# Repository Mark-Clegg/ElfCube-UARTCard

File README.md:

# Elf-Cube - UART Card
Simple retro computer based on the 1802 series of processors.

Provides serial I/O to the ElfCube using either the onboard DB-9 connector, or via the USB connector on the Backplane.

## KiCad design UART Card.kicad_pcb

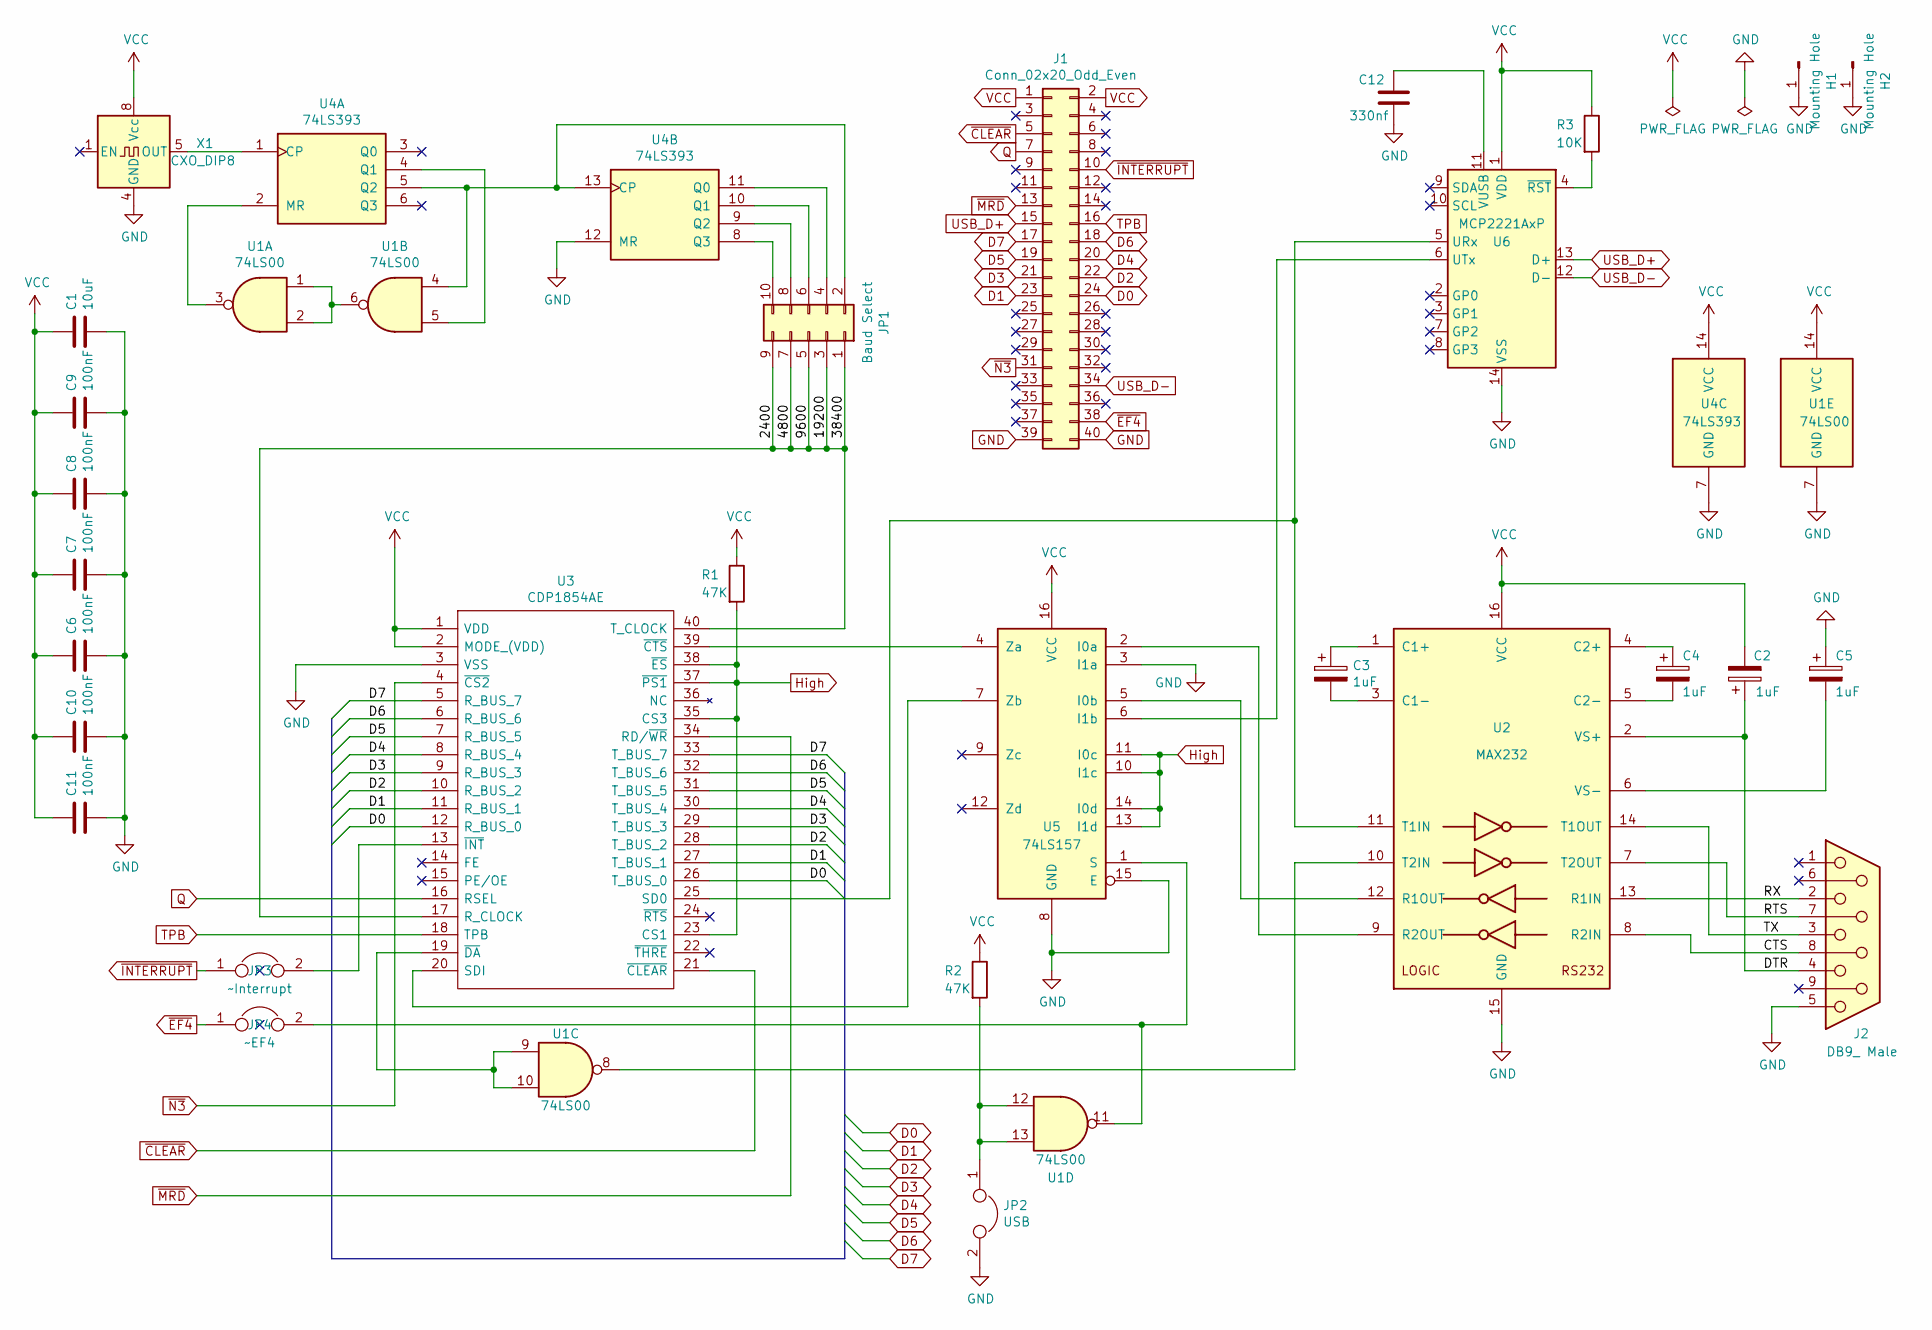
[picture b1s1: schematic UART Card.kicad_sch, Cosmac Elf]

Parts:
C1: 10uF; CP_Radial_D5.0mm_P2.50mm
C2, C3, C4, C5: 1uF; CP_Radial_D5.0mm_P2.50mm
C6, C7, C8, C9, C10, C11: 100nF; C_Disc_D3.8mm_W2.6mm_P2.50mm
C12: 330nf; C_Rect_L7.0mm_W3.5mm_P5.00mm
H1, H2: Mounting Hole; MountingHole_3.2mm_M3_Pad_Via
J1: Conn_02x20_Odd_Even; PinHeader_2x20_P2.54mm_Horizontal
J2: DB9_ Male; DSUB-9_Male_Horizontal_P2.77x2.84mm_EdgePinOffset9.90mm_Hou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
JP1: Baud Select; PinHeader_2x05_P2.54mm_Vertical
JP2: USB; PinHeader_1x02_P2.54mm_Vertical
JP3: ~Interrupt; PinHeader_1x02_P2.54mm_Vertical
JP4: ~EF4; PinHeader_1x02_P2.54mm_Vertical
R1, R2: 47K; R_Axial_DIN0207_L6.3mm_D2.5mm_P7.62mm_Horizontal
R3: 10K; R_Axial_DIN0207_L6.3mm_D2.5mm_P7.62mm_Horizontal
U1: 74LS00; DIP-14_W7.62mm
U2: MAX232; DIP-16_W7.62mm
U3: CDP1854AE; DIP-40_W15.24mm_Socket; Manufacturer_Part_Number CDP1854AE; Mouser Part Number N/A
U4: 74LS393; DIP-14_W7.62mm
U5: 74LS157; DIP-16_W7.62mm
U6: MCP2221AxP; DIP-14_W7.62mm
X1: CXO_DIP8; Oscillator_DIP-8

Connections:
/19200: JP1.1, JP1.3, JP1.5, JP1.7, JP1.9, U3.17 (R_CLOCK), U3.40 (T_CLOCK)
/CTS: J2.8, U2.8 (R2IN)
/DTR: C2.1, J2.4, U2.2 (VS+)
/RTS: J2.7, U2.7 (T2OUT)
/RX: J2.2, U2.13 (R1IN)
/TX: J2.3, U2.14 (T1OUT)
D0: J1.24, U3.12 (R_BUS_0), U3.26 (T_BUS_0)
D1: J1.23, U3.11 (R_BUS_1), U3.27 (T_BUS_1)
D2: J1.22, U3.10 (R_BUS_2), U3.28 (T_BUS_2)
D3: J1.21, U3.9 (R_BUS_3), U3.29 (T_BUS_3)
D4: J1.20, U3.8 (R_BUS_4), U3.30 (T_BUS_4)
D5: J1.19, U3.7 (R_BUS_5), U3.31 (T_BUS_5)
D6: J1.18, U3.6 (R_BUS_6), U3.32 (T_BUS_6)
D7: J1.17, U3.5 (R_BUS_7), U3.33 (T_BUS_7)
GND: C1.2, C5.1, C6.2, C7.2, C8.2, C9.2, C10.2, C11.2, C12.2, H1.1, H2.1, J1.39, J1.40, J2.5, JP2.2, U1.7 (GND), U2.15 (GND), U3.3 (VSS), U4.7 (GND), U4.12 (MR), U5.3 (I1a), U5.8 (GND), U5.15 (E), U6.14 (VSS), X1.4 (GND)
High: R1.2, U3.23 (CS1), U3.35 (CS3), U3.37 (~PS1), U3.38 (~ES), U5.10 (I1c), U5.11 (I0c), U5.13 (I1d), U5.14 (I0d)
unnamed: JP1.2, U1.4, U4.5 (Q2), U4.13 (CP)
unnamed: JP1.4, U4.11 (Q0)
unnamed: JP1.6, U4.10 (Q1)
unnamed: JP1.8, U4.9 (Q2)
unnamed: JP1.10, U4.8 (Q3)
unnamed: JP2.1, R2.2, U1.12, U1.13
unnamed: U1.1, U1.2, U1.6
unnamed: C3.1, U2.1 (C1+)
unnamed: C3.2, U2.3 (C1-)
unnamed: C4.1, U2.4 (C2+)
unnamed: C4.2, U2.5 (C2-)
unnamed: U2.12 (R1OUT), U5.5 (I0b)
unnamed: U2.9 (R2OUT), U5.2 (I0a)
unnamed: U2.11 (T1IN), U3.25 (SD0), U6.5 (URx)
unnamed: U1.8, U2.10 (T2IN)
unnamed: C5.2, U2.6 (VS-)
unnamed: U3.20 (SDI), U5.7 (Zb)
unnamed: U3.39 (~CTS), U5.4 (Za)
unnamed: U1.9, U1.10, U3.19 (~DA)
unnamed: JP3.2, U3.13 (~INT)
unnamed: U4.1 (CP), X1.5 (OUT)
unnamed: U1.3, U4.2 (MR)
unnamed: U1.5, U4.4 (Q1)
unnamed: U5.6 (I1b), U6.6 (UTx)
unnamed: JP4.2, U1.11, U5.1 (S)
unnamed: C12.1, U6.11 (VUSB)
unnamed: R3.2, U6.4 (~RST)
Q: J1.7, U3.16 (RSEL)
TPB: J1.16, U3.18 (TPB)
USB_D+: J1.15, U6.13 (D+)
USB_D-: J1.34, U6.12 (D-)
VCC: C1.1, C2.2, C6.1, C7.1, C8.1, C9.1, C10.1, C11.1, J1.1, J1.2, R1.1, R2.1, R3.1, U1.14 (VCC), U2.16 (VCC), U3.1 (VDD), U3.2 (MODE_(VDD)), U4.14 (VCC), U5.16 (VCC), U6.1 (VDD), X1.8 (Vcc)
~CLEAR: J1.5, U3.21 (~CLEAR)
~EF4: J1.38, JP4.1
~INTERRUPT: J1.10, JP3.1
~MRD: J1.13, U3.34 (RD/~WR)
~N3: J1.31, U3.4 (~CS2)

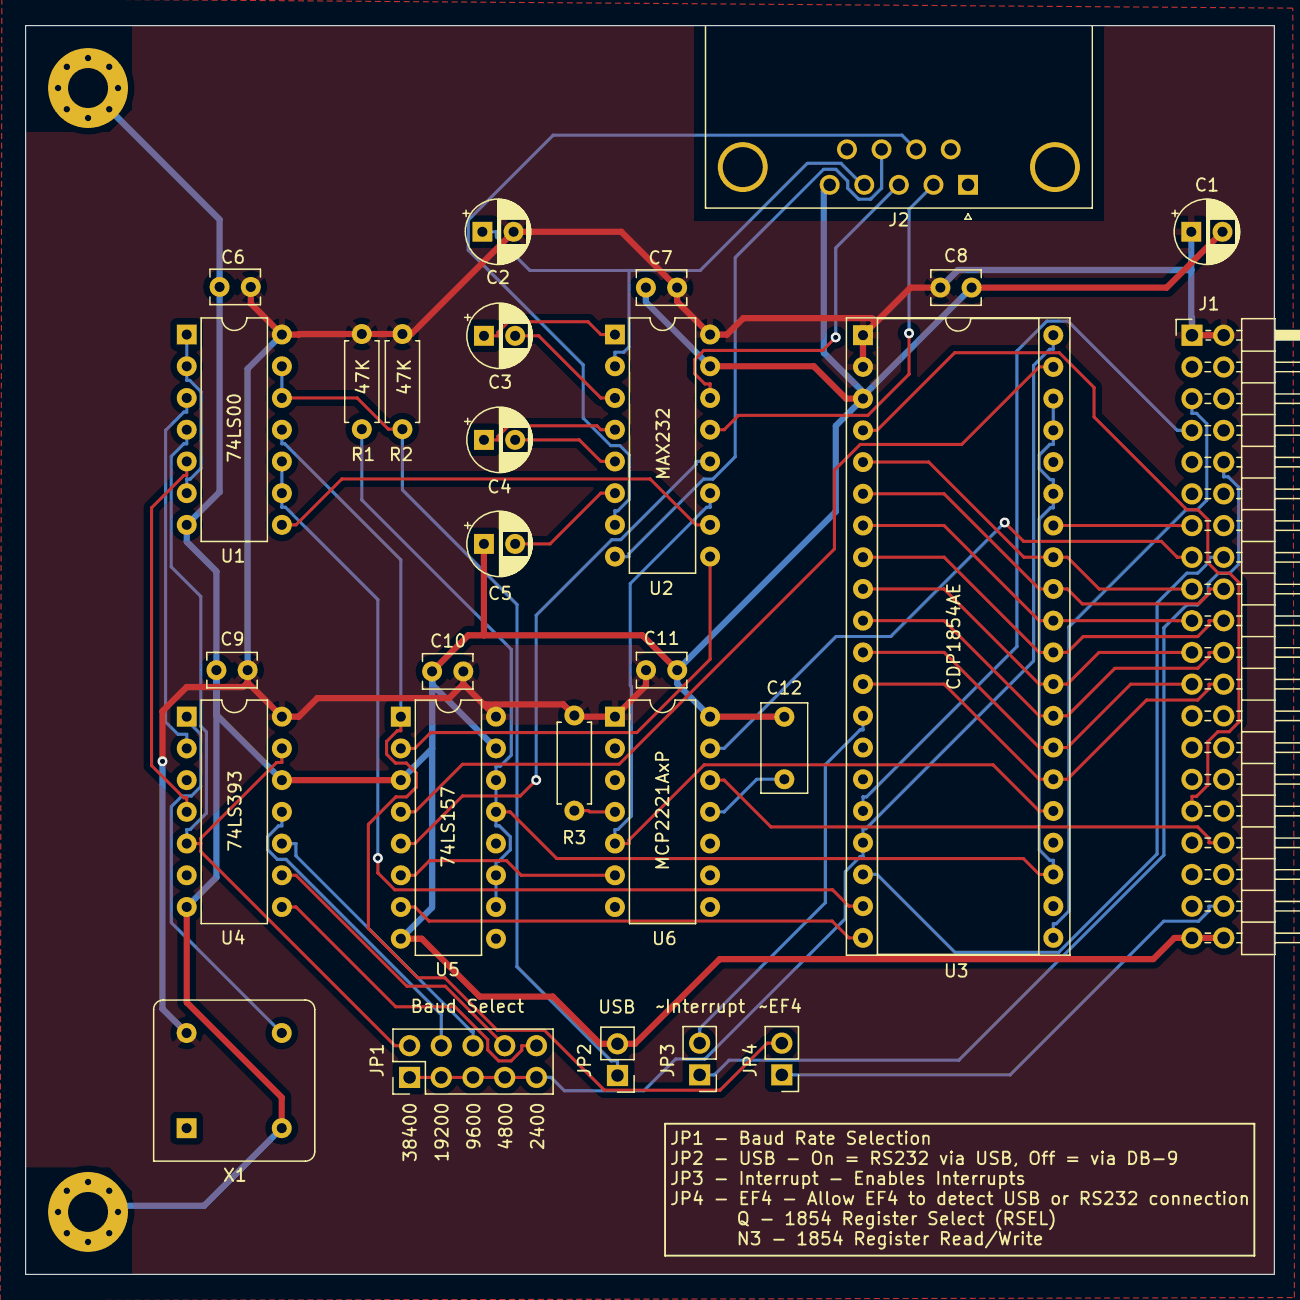
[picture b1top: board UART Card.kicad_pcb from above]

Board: 2 copper layers, 100.0 x 100.0 mm, 30 parts (0 on the bottom side), 53 nets.

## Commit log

2021-11-06 Rev 1.0
2021-11-06 Added README.md
2021-11-08 Updated wiki
2023-11-29 Disconnect ~CLEAR from USB Controller
2023-11-29 Remove old .pro file
2023-11-29 Updated .gitignore
